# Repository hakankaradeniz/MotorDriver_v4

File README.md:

# MotorDriver_v4
MotorDriver_v4 updated by me

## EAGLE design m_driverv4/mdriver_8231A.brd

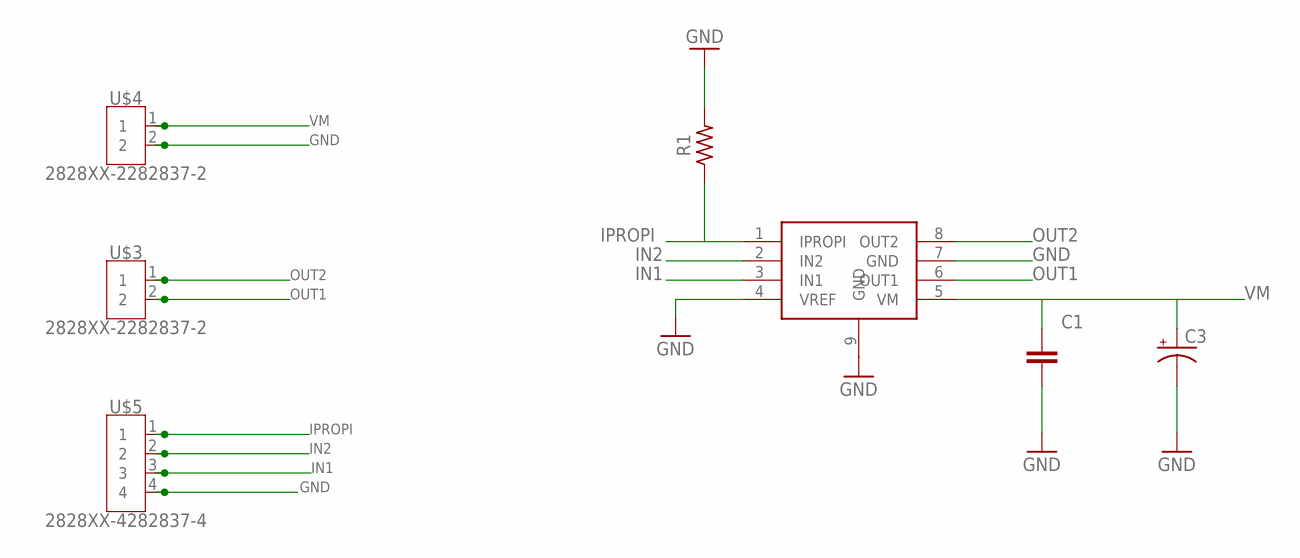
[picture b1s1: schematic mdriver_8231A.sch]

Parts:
C1: C_CHIP-1206(3216-METRIC); CAPC3216X135
C3: C-POL-US_ECAP-10.5MM; CAPAE1030X1050N
R1: R-US_CHIP-0603(1608-METRIC); RESC1608X60
U$1: DRV8231A; SOIC127P580X170-9T271X340N
U$3, U$4: 2828XX-2282837-2; TERMBLK_508-2N
U$5: 2828XX-4282837-4; TERMBLK_508-4N

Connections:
GND: C1.2, C3.2 (-), R1.2, U$1.4 (VREF), U$1.7 (GND), U$1.9 (GND), U$4.2, U$5.4
IN1: U$1.3 (IN1), U$5.3
IN2: U$1.2 (IN2), U$5.2
IPROPI: R1.1, U$1.1 (IPROPI), U$5.1
OUT1: U$1.6 (OUT1), U$3.2
OUT2: U$1.8 (OUT2), U$3.1
VM: C1.1, C3.1 (+), U$1.5 (VM), U$4.1

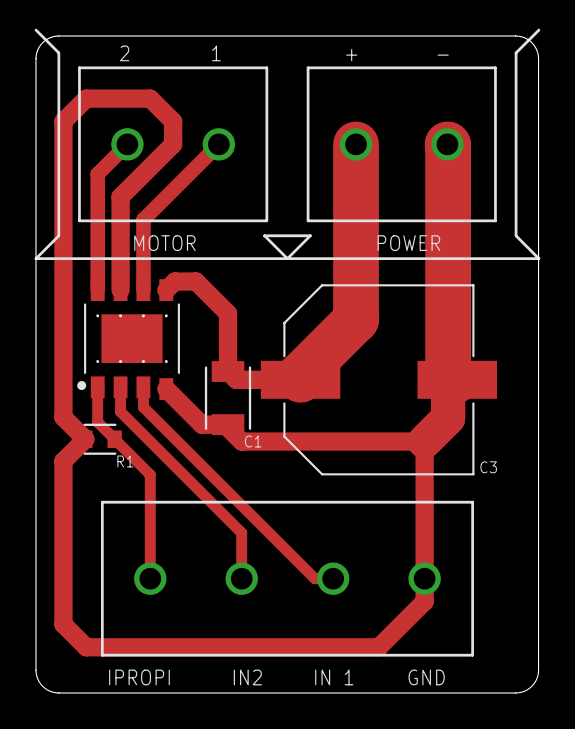
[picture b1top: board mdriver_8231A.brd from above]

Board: 2 copper layers, 27.9 x 36.5 mm, 7 parts (0 on the bottom side), 7 nets.
